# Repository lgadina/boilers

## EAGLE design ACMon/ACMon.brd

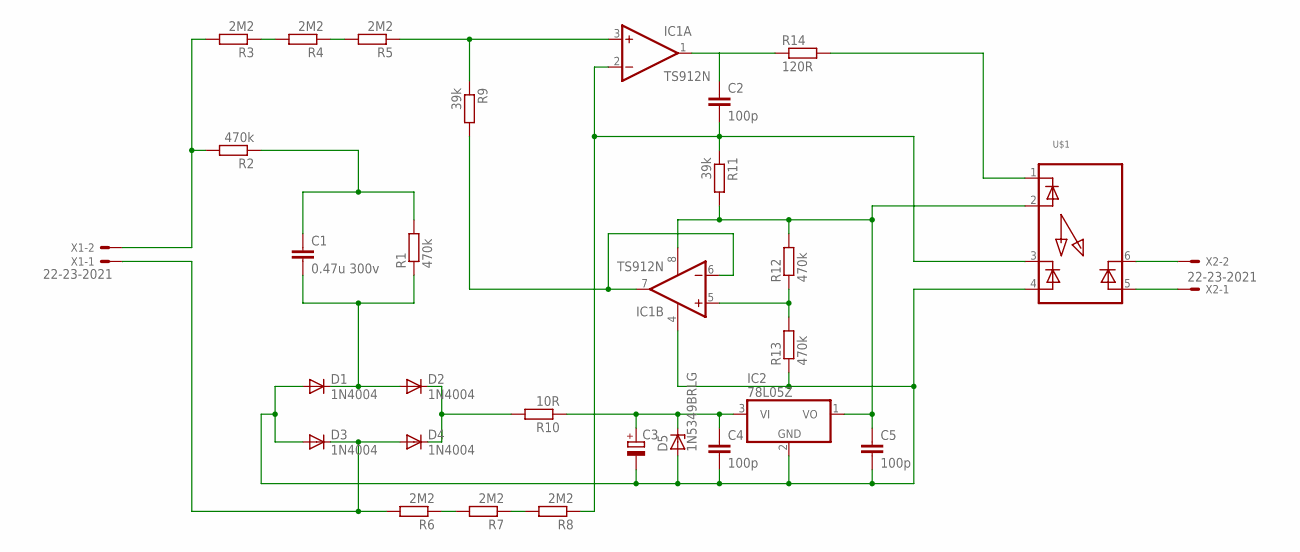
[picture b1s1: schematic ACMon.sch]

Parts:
C1: 0.47u 300v; C275-113X316
C2, C4, C5: 100p; C050-025X075
C3: CPOL-EUE3.5-8; E3,5-8
D1, D2, D3, D4: 1N4004; DO41-10
D5: 1N5349BRLG; DO41Z10
IC1: TS912N; DIL08
IC2: 78L05Z; TO92
R1, R2, R12, R13: 470k; 0309/12
R3, R4, R5, R6, R7, R8: 2M2; 0309/12
R9, R11: 39k; 0309/12
R10: 10R; 0309/12
R14: 120R; 0309/12
U$1: IL300; DIL08
X1, X2: 22-23-2021

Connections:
unnamed: C1.1, R1.2, R2.1
unnamed: C1.2, D1.C, D2.A, R1.1
unnamed: C3.-, C4.2, C5.2, D1.A, D3.A, D5.A, IC1.4 (V-), IC2.2 (GND), R13.1, U$1.4
unnamed: D3.C, D4.A, R6.2, X1.1
unnamed: R6.1, R7.2
unnamed: D2.C, D4.C, R10.2
unnamed: R2.2, R3.2, X1.2
unnamed: R3.1, R4.2
unnamed: R4.1, R5.2
unnamed: IC1.3 (+IN), R5.1, R9.1
unnamed: IC1.6 (-IN), IC1.7 (OUT), R9.2
unnamed: R7.1, R8.2
unnamed: C2.2, IC1.2 (-IN), R8.1, R11.1, U$1.3
unnamed: C2.1, IC1.1 (OUT), R14.1
unnamed: R14.2, U$1.1
unnamed: C3.+, C4.1, D5.C, IC2.3 (VI), R10.1
unnamed: U$1.6, X2.2
unnamed: C5.1, IC1.8 (V+), IC2.1 (VO), R11.2, R12.2, U$1.2
unnamed: U$1.5, X2.1
unnamed: IC1.5 (+IN), R12.1, R13.2

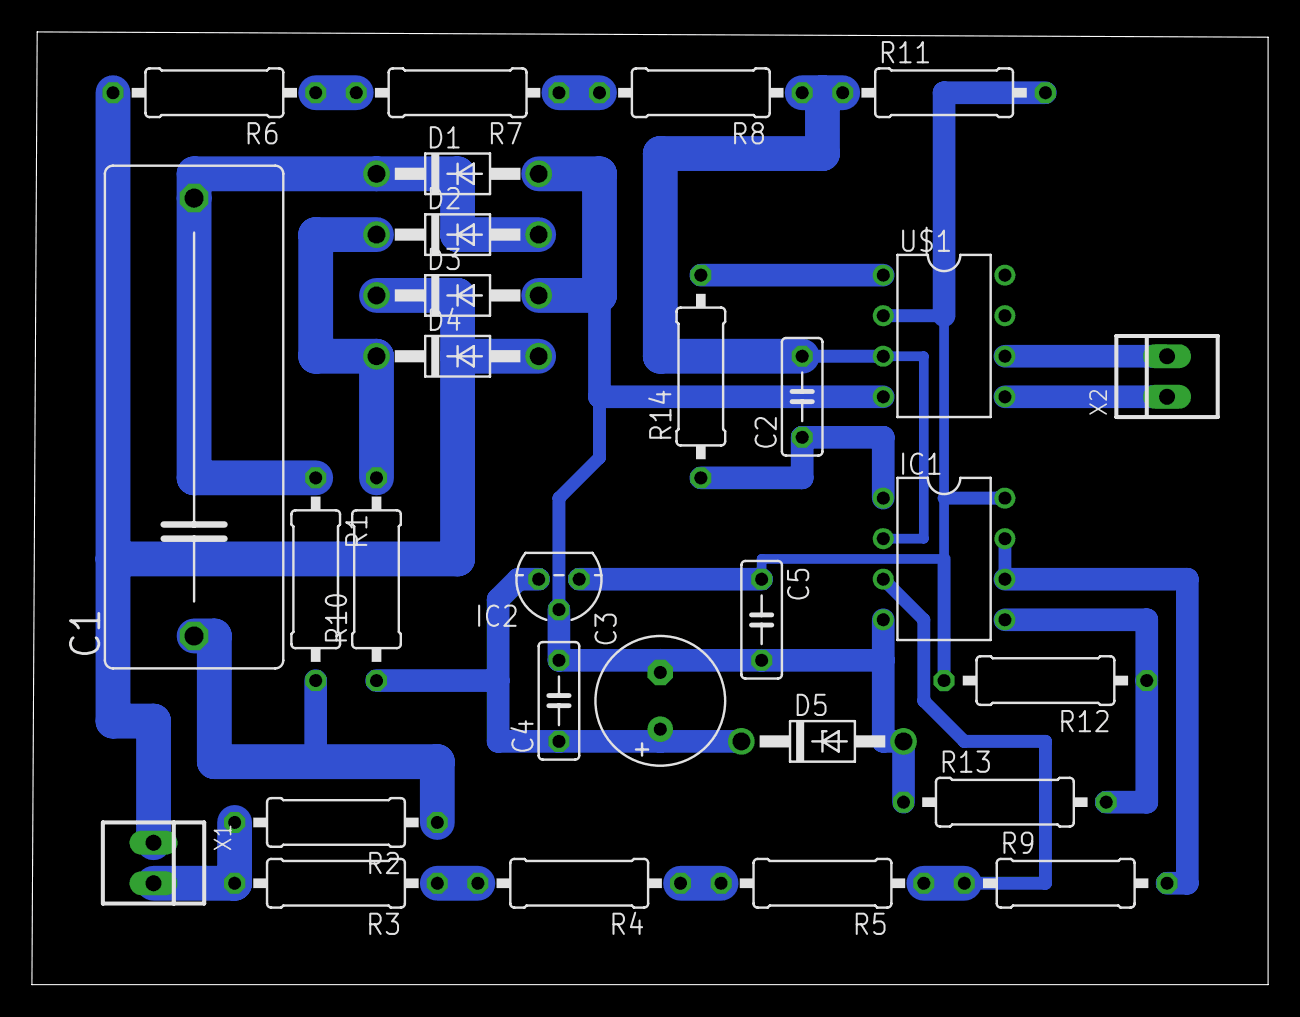
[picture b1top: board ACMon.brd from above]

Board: 2 copper layers, 77.5 x 59.7 mm, 29 parts (0 on the bottom side), 20 nets.

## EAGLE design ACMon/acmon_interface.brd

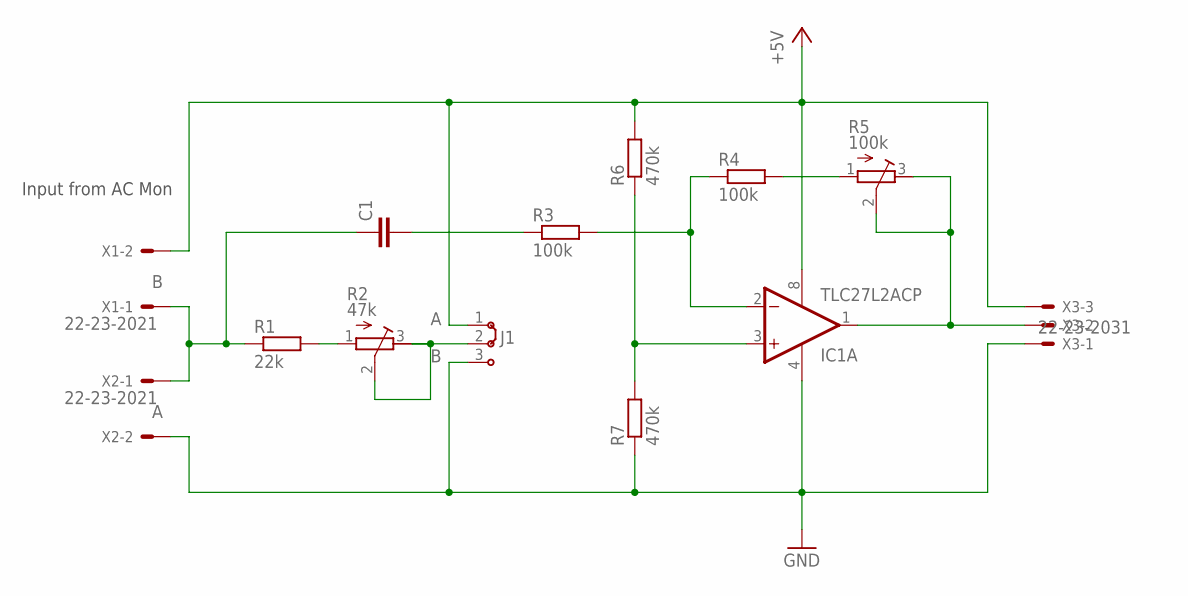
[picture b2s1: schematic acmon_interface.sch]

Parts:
C1: C-EU050-030X075; C050-030X075
IC1: TLC27L2ACP; DIL08
J1: J2X2MM; 04C
R1: 22k; 0207/10
R2: 47k; RTRIM64Y
R3, R4: 100k; 0207/10
R5: 100k; RTRIM64Y
R6, R7: 470k; 0207/10
X1, X2: 22-23-2021
X3: 22-23-2031

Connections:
+5V: IC1.8 (VDD), J1.1, R6.2, X1.2, X3.3
GND: IC1.4 (GND), J1.3, R7.1, X2.2, X3.1
unnamed: J1.2, R2.2 (S), R2.3 (E)
unnamed: R1.2, R2.1 (A)
unnamed: C1.1, R1.1, X1.1, X2.1
unnamed: IC1.2 (-IN), R3.2, R4.1
unnamed: R4.2, R5.1 (A)
unnamed: IC1.1 (OUT), R5.2 (S), R5.3 (E), X3.2
unnamed: C1.2, R3.1
unnamed: IC1.3 (+IN), R6.1, R7.2

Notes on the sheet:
Input from AC Mon

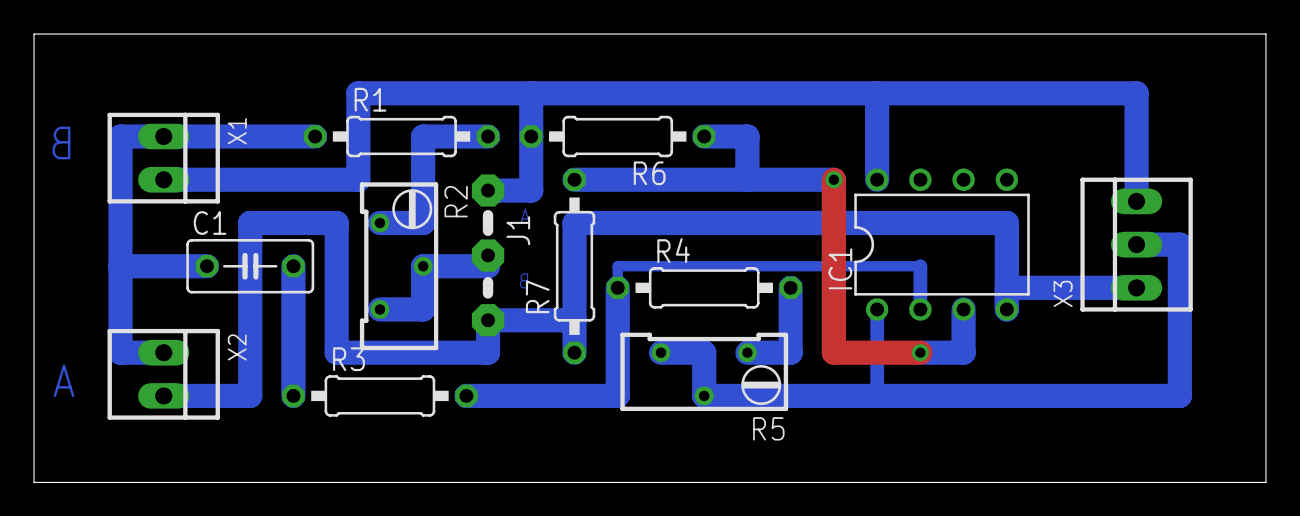
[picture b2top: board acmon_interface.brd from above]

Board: 2 copper layers, 72.4 x 26.3 mm, 13 parts (0 on the bottom side), 10 nets.

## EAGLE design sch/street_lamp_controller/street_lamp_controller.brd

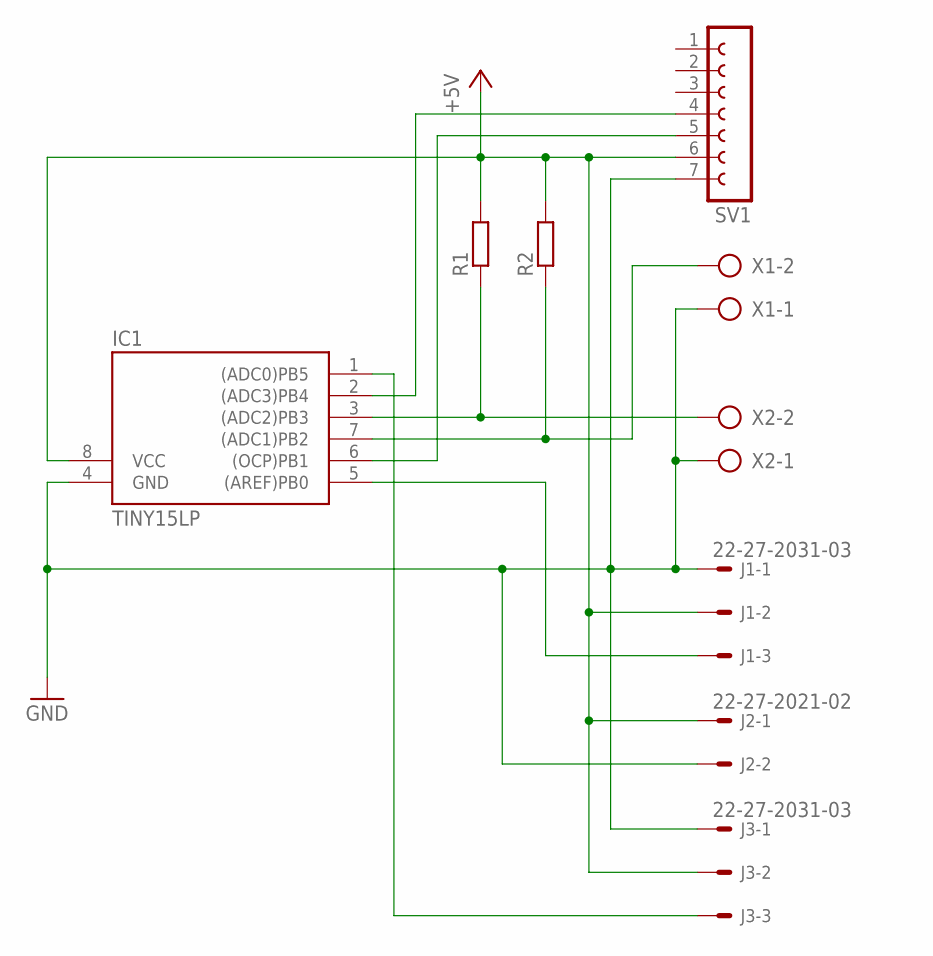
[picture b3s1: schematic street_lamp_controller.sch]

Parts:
IC1: TINY15LP; DIL08
J1, J3: 22-27-2031-03; 6410-03
J2: 22-27-2021-02; 6410-02
R1, R2: R-EU_0204/5; 0204/5
SV1: FE07-1; FE07
X1, X2: AK300/2

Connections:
+5V: IC1.8 (VCC), J1.2, J2.1, J3.2, R1.2, R2.2, SV1.6
GND: IC1.4 (GND), J1.1, J2.2, J3.1, SV1.7, X1.1, X2.1
unnamed: IC1.6 ((OCP)PB1), SV1.5
unnamed: IC1.7 ((ADC1)PB2), R2.1, X1.2
unnamed: IC1.3 ((ADC2)PB3), R1.1, X2.2
unnamed: IC1.5 ((AREF)PB0), J1.3
unnamed: IC1.2 ((ADC3)PB4), SV1.4
unnamed: IC1.1 ((ADC0)PB5), J3.3

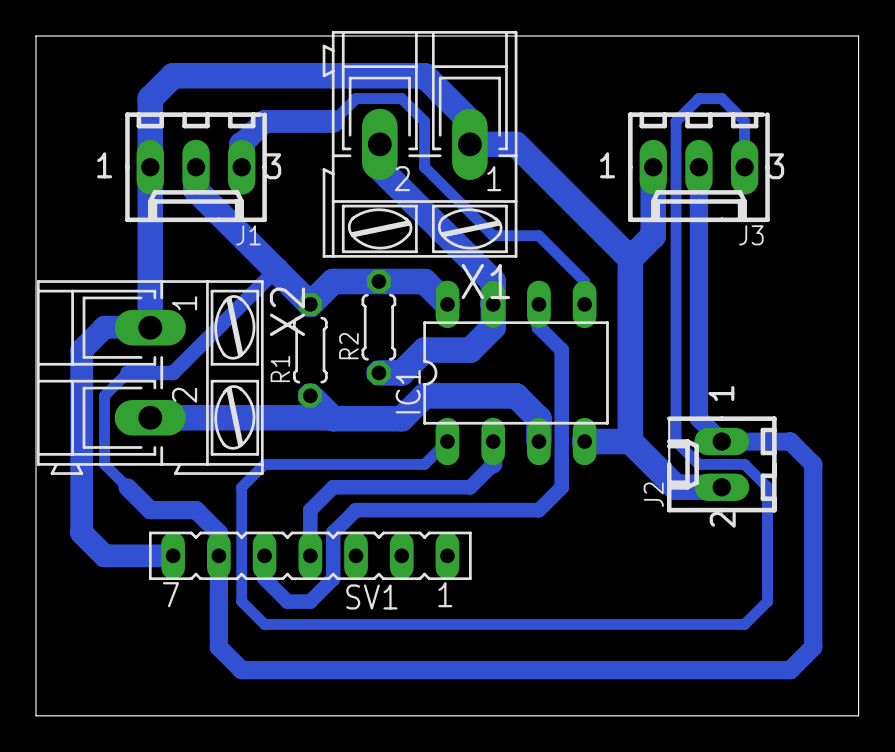
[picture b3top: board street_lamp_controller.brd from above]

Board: 2 copper layers, 45.7 x 37.8 mm, 9 parts (0 on the bottom side), 8 nets.

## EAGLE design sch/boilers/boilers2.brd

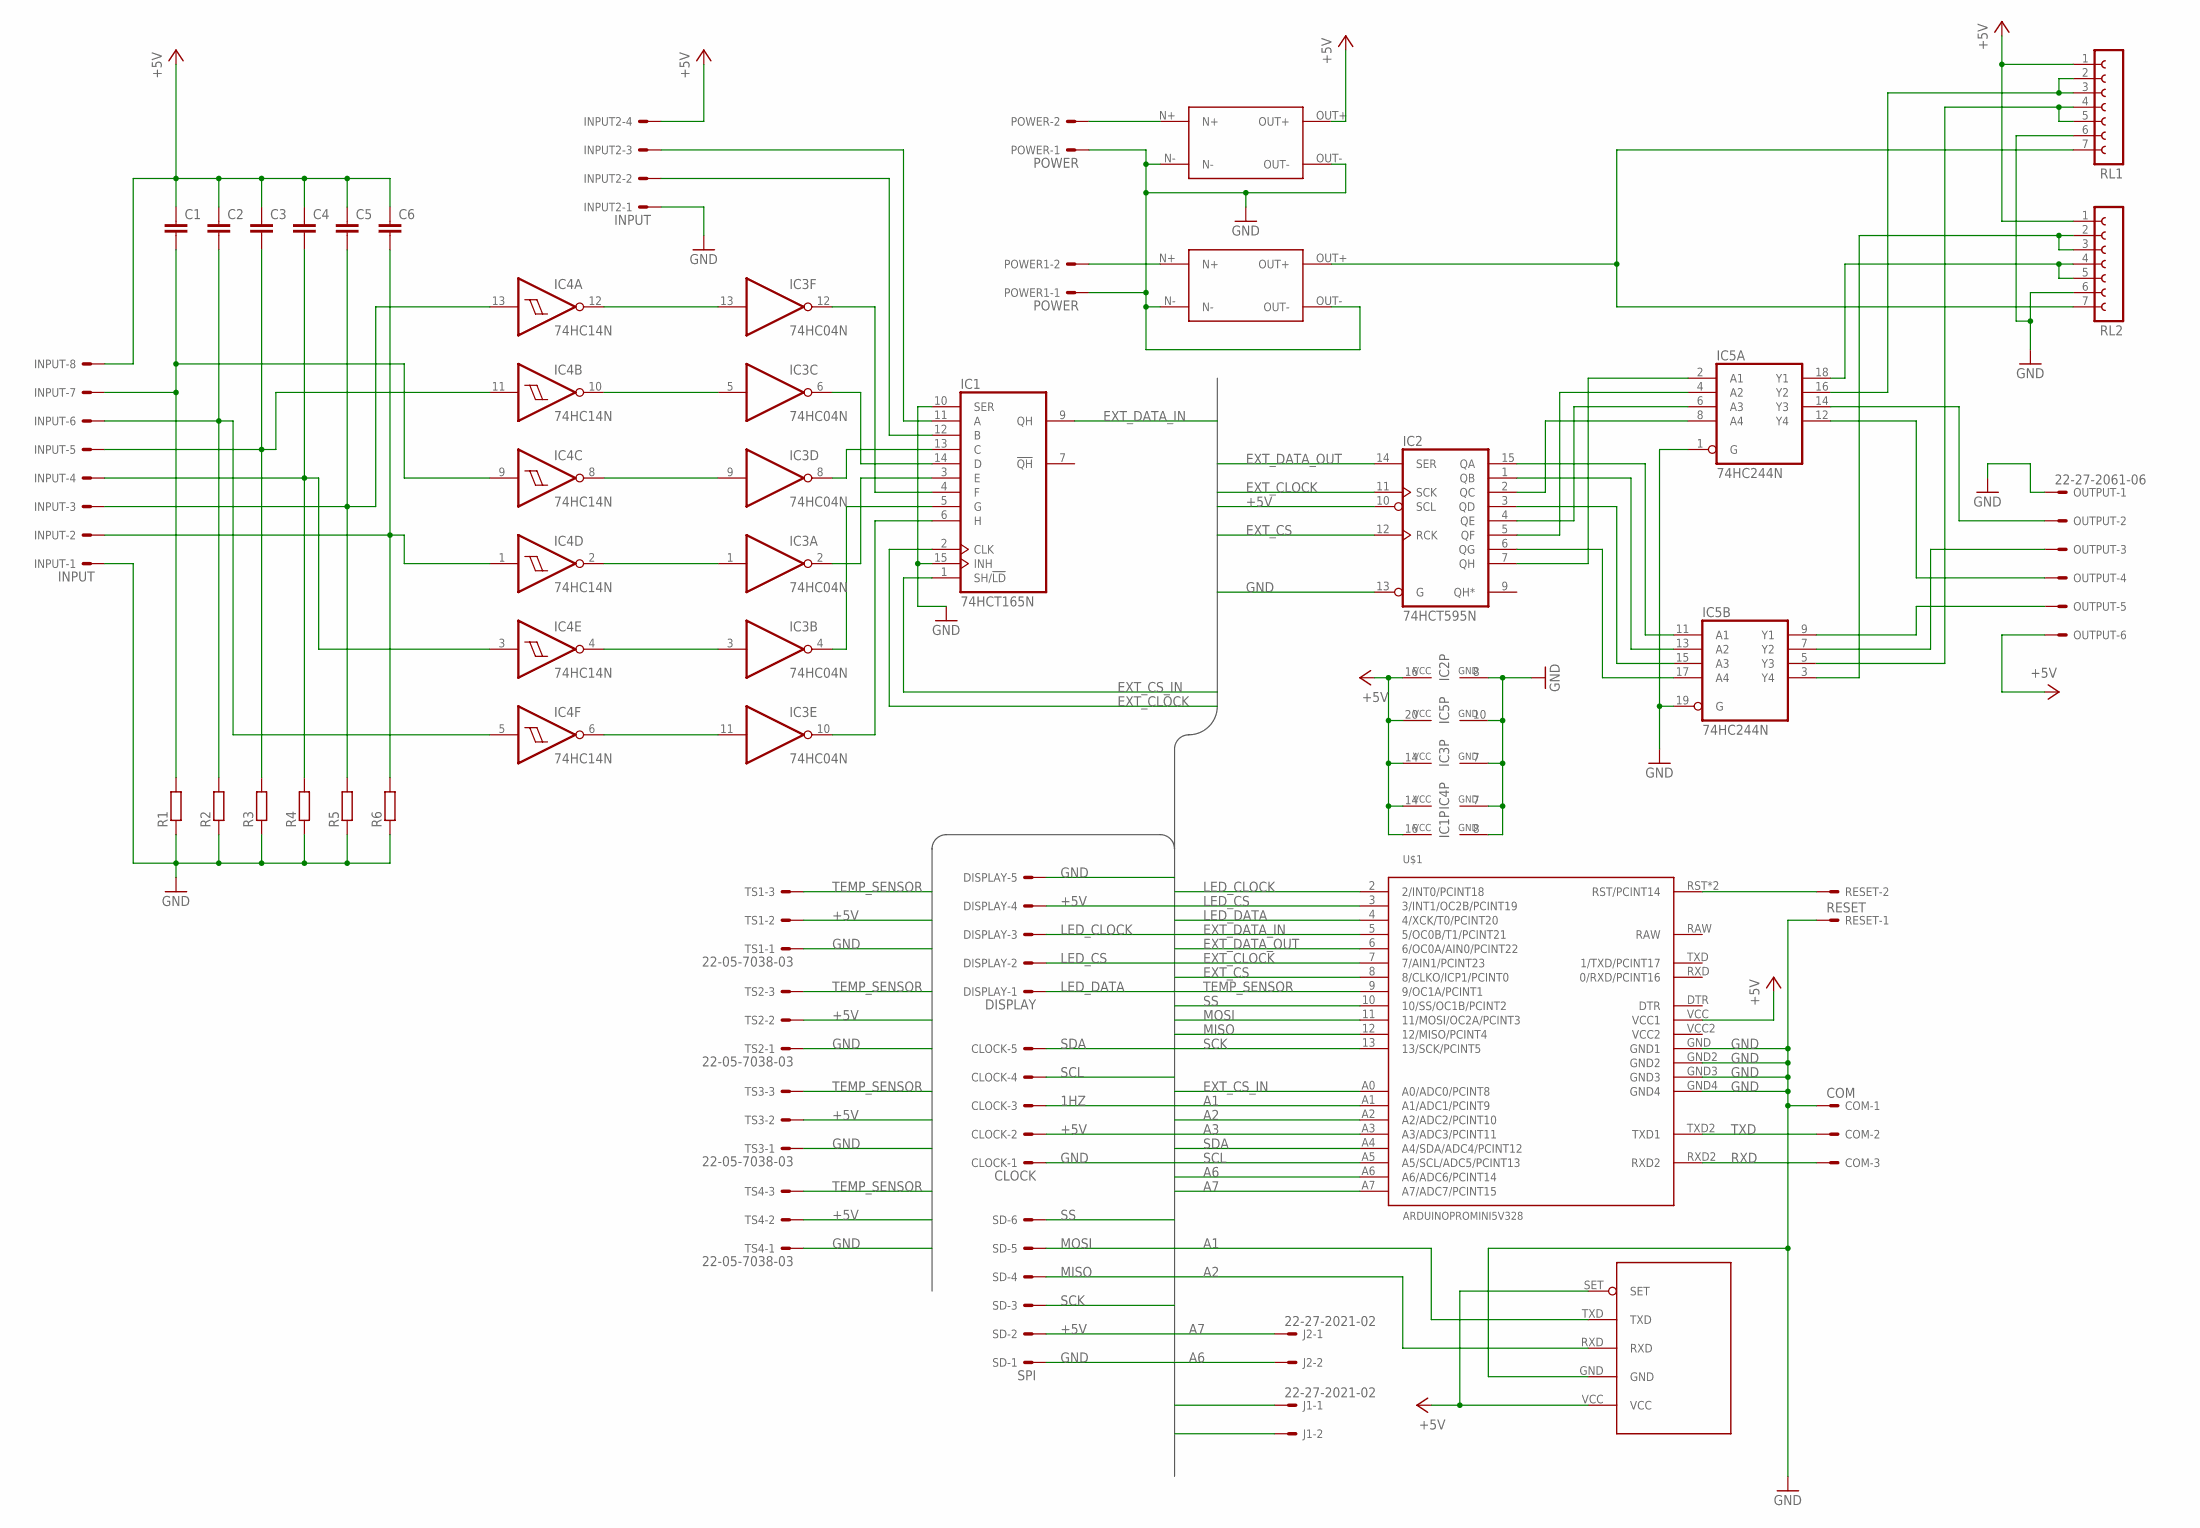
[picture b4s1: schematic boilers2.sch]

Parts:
C1, C2, C3, C4, C5, C6: C-EU050-025X075; C050-025X075
CLOCK: CLOCK; 6410-05
COM: COM; 6410-03
DISPLAY: DISPLAY; 6410-05
IC1: 74HCT165N; DIL16
IC2: 74HCT595N; DIL16
IC3: 74HC04N; DIL14
IC4: 74HC14N; DIL14
IC5: 74HC244N; DIL20
INPUT: INPUT; 6410-08
INPUT2: INPUT; 6410-04
J1, J2: 22-27-2021-02; 6410-02
OUTPUT: 22-27-2061-06; 6410-06
POWER, POWER1: POWER; 6410-02
R1, R2, R3, R4, R5, R6: R-EU_0411/15; 0411/15
RESET: RESET; 6410-02
RL1, RL2: FE07-1; FE07
SD: SPI; 6410-06
TS1, TS2, TS3, TS4: 22-05-7038-03; 7395-03
U$1: ARDUINOPROMINI5V328; ARDUINOMINIPRO5V328
U$4, U$5: 5V_STAB
U$6: HC-11

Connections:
1HZ: CLOCK.3
+5V: C1.1, C2.1, C3.1, C4.1, C5.1, C6.1, CLOCK.2, DISPLAY.4, IC1.16 (VCC), IC2.10 (SCL), IC2.16 (VCC), IC3.14 (VCC), IC4.14 (VCC), IC5.20 (VCC), INPUT.8, INPUT2.4, J1.1, OUTPUT.6, RL1.1, RL2.1, SD.2, TS1.2, TS2.2, TS3.2, TS4.2, U$1.VCC (VCC1), U$4.OUT+, U$6.SET, U$6.VCC
A1: U$1.A1 (A1/ADC1/PCINT9), U$6.TXD
A2: U$1.A2 (A2/ADC2/PCINT10), U$6.RXD
A3: J1.2, U$1.A3 (A3/ADC3/PCINT11)
A6: J2.2, U$1.A6 (A6/ADC6/PCINT14)
A7: J2.1, U$1.A7 (A7/ADC7/PCINT15)
EXT_CLOCK: IC1.2 (CLK), IC2.11 (SCK), U$1.7 (7/AIN1/PCINT23)
EXT_CS: IC2.12 (RCK), U$1.8 (8/CLKO/ICP1/PCINT0)
EXT_CS_IN: IC1.1 (SH/!LD), U$1.A0 (A0/ADC0/PCINT8)
EXT_DATA_IN: IC1.9 (QH), U$1.5 (5/OC0B/T1/PCINT21)
EXT_DATA_OUT: IC2.14 (SER), U$1.6 (6/OC0A/AIN0/PCINT22)
GND: CLOCK.1, COM.1, DISPLAY.5, IC1.8 (GND), IC1.10 (SER), IC1.15 (INH), IC2.8 (GND), IC2.13 (G), IC3.7 (GND), IC4.7 (GND), IC5.1 (G), IC5.10 (GND), IC5.19 (G), INPUT.1, INPUT2.1, OUTPUT.1, POWER.1, POWER1.1, R1.1, R2.1, R3.1, R4.1, R5.1, R6.1, RESET.1, RL1.6, RL2.6, SD.1, TS1.1, TS2.1, TS3.1, TS4.1, U$1.GND (GND1), U$1.GND2, U$1.GND3, U$1.GND4, U$4.N-, U$4.OUT-, U$5.N-, U$5.OUT-, U$6.GND
LED_CLOCK: DISPLAY.3, U$1.2 (2/INT0/PCINT18)
LED_CS: DISPLAY.2, U$1.3 (3/INT1/OC2B/PCINT19)
LED_DATA: DISPLAY.1, U$1.4 (4/XCK/T0/PCINT20)
MISO: SD.4, U$1.12 (12/MISO/PCINT4)
MOSI: SD.5, U$1.11 (11/MOSI/OC2A/PCINT3)
unnamed: IC3.13 (I), IC4.12 (O)
unnamed: IC3.5 (I), IC4.10 (O)
unnamed: IC3.9 (I), IC4.8 (O)
unnamed: IC3.1 (I), IC4.2 (O)
unnamed: IC3.3 (I), IC4.4 (O)
unnamed: IC3.11 (I), IC4.6 (O)
unnamed: IC2.15 (QA), IC5.11 (A1)
unnamed: IC2.1 (QB), IC5.13 (A2)
unnamed: IC2.3 (QD), IC5.15 (A3)
unnamed: IC2.6 (QG), IC5.17 (A4)
unnamed: IC2.7 (QH), IC5.2 (A1)
unnamed: IC2.2 (QC), IC5.8 (A4)
unnamed: IC2.4 (QE), IC5.6 (A3)
unnamed: IC2.5 (QF), IC5.4 (A2)
unnamed: IC1.11 (A), INPUT2.3
unnamed: IC1.5 (G), IC3.4 (O)
unnamed: IC1.6 (H), IC3.10 (O)
unnamed: IC1.3 (E), IC3.2 (O)
unnamed: IC1.13 (C), IC3.8 (O)
unnamed: IC1.14 (D), IC3.6 (O)
unnamed: IC1.4 (F), IC3.12 (O)
unnamed: C1.2, IC4.9 (I), INPUT.7, R1.2
unnamed: C2.2, IC4.5 (I), INPUT.6, R2.2
unnamed: IC1.12 (B), INPUT2.2
unnamed: IC5.16 (Y2), RL1.2, RL1.3
unnamed: C5.2, IC4.13 (I), INPUT.3, R5.2
unnamed: C6.2, IC4.1 (I), INPUT.2, R6.2
unnamed: IC5.3 (Y4), RL2.2, RL2.3
unnamed: C3.2, IC4.11 (I), INPUT.5, R3.2
unnamed: C4.2, IC4.3 (I), INPUT.4, R4.2
unnamed: IC5.18 (Y1), RL2.4, RL2.5
unnamed: IC5.5 (Y3), RL1.4, RL1.5
unnamed: IC5.14 (Y3), OUTPUT.2
unnamed: IC5.7 (Y2), OUTPUT.3
unnamed: IC5.12 (Y4), OUTPUT.4
unnamed: IC5.9 (Y1), OUTPUT.5
unnamed: POWER.2, U$4.N+
unnamed: RL1.7, RL2.7, U$5.OUT+
unnamed: RESET.2, U$1.RST (RST/PCINT14), U$1.RST2 (RST/PCINT14)
unnamed: POWER1.2, U$5.N+
RXD: COM.3, U$1.RXD2
SCK: SD.3, U$1.13 (13/SCK/PCINT5)
SCL: CLOCK.4, U$1.A5 (A5/SCL/ADC5/PCINT13)
SDA: CLOCK.5, U$1.A4 (A4/SDA/ADC4/PCINT12)
SS: SD.6, U$1.10 (10/SS/OC1B/PCINT2)
TEMP_SENSOR: TS1.3, TS2.3, TS3.3, TS4.3, U$1.9 (9/OC1A/PCINT1)
TXD: COM.2, U$1.TXD2 (TXD1)
VCC2: U$1.VCC2

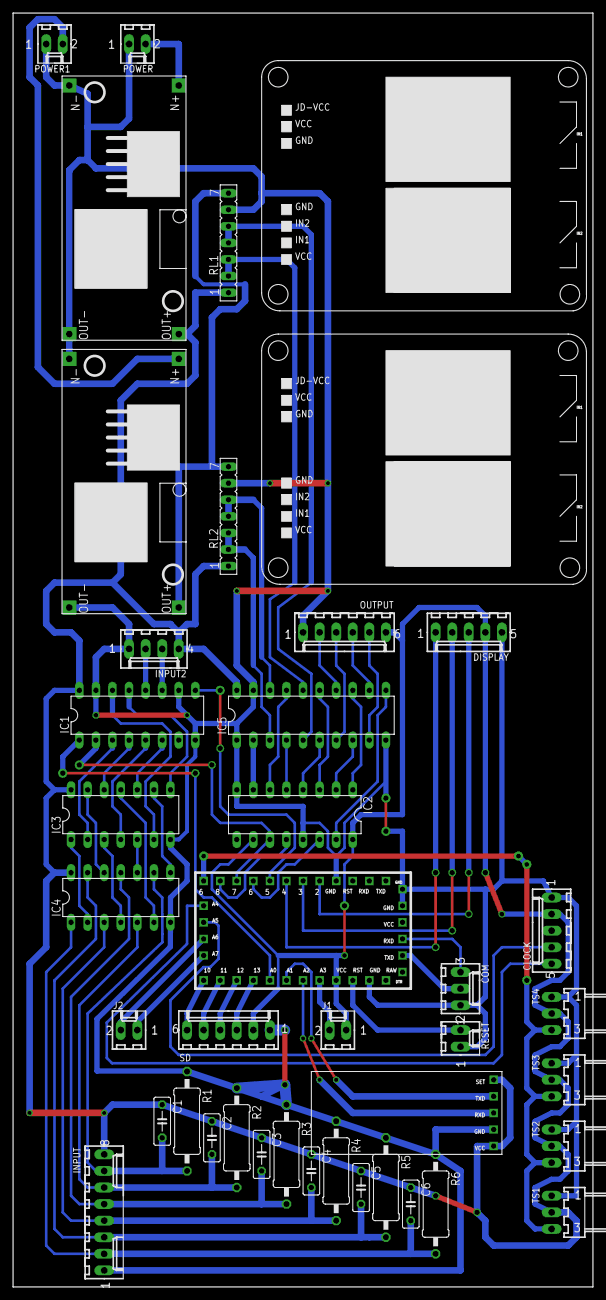
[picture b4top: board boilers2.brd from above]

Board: 2 copper layers, 88.9 x 195.2 mm, 41 parts (0 on the bottom side), 64 nets.

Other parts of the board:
U$2, U$3: 2CHAN_RELAY_5V

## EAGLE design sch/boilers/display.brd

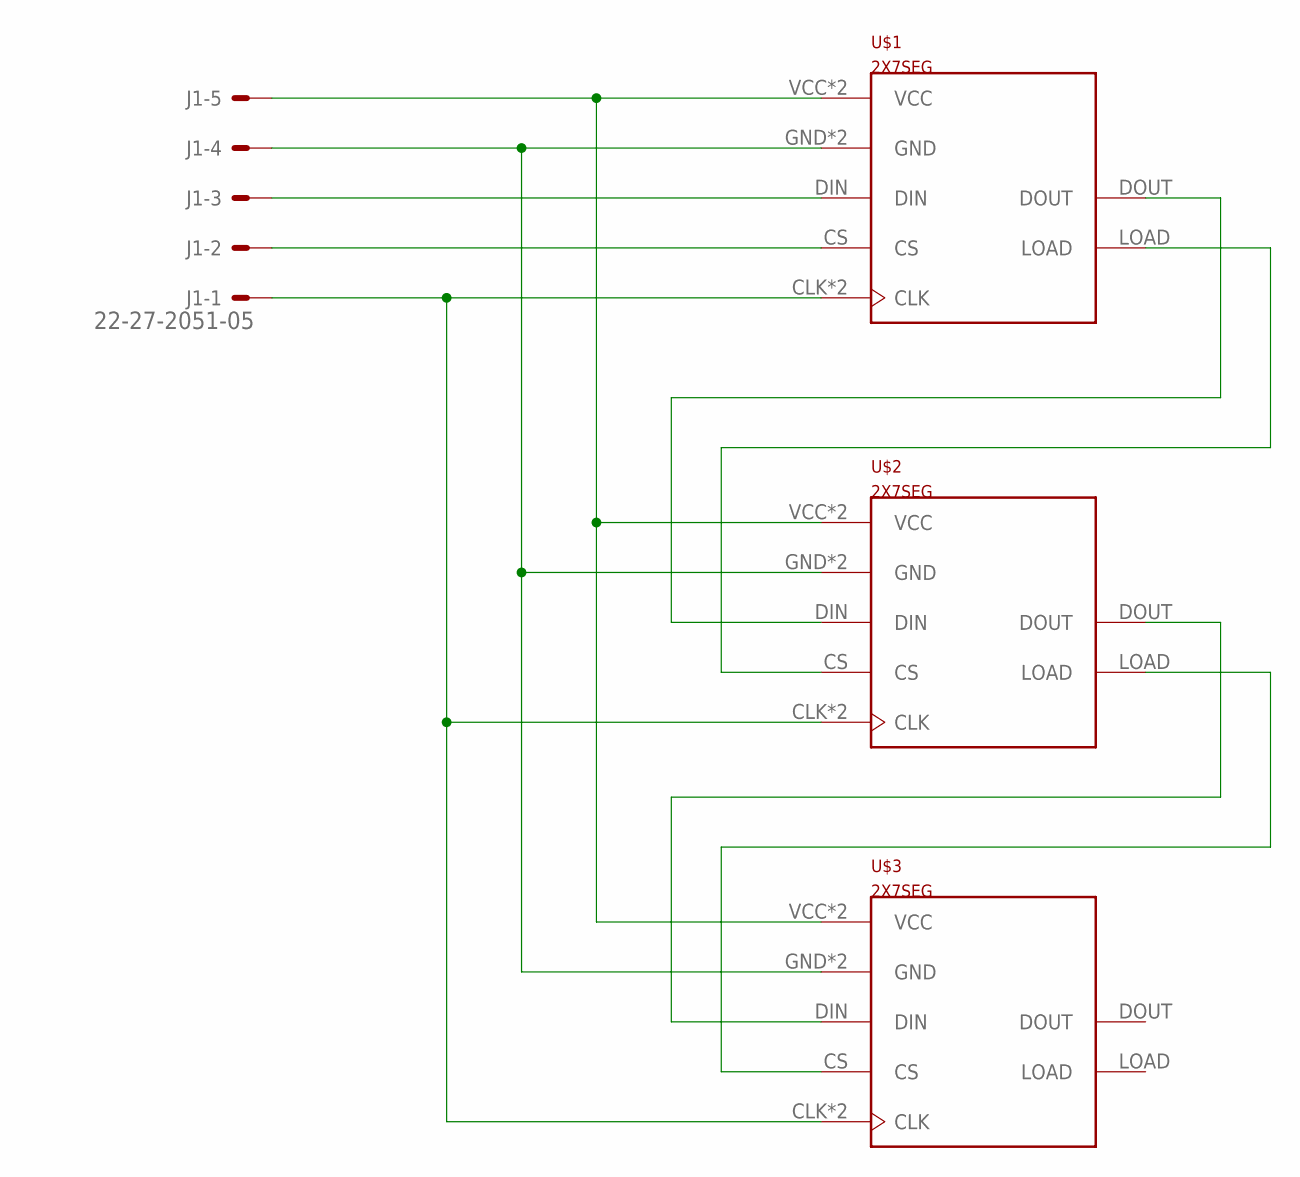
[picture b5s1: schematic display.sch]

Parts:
J1: 22-27-2051-05; 6410-05
U$1, U$2, U$3: 2X7SEG

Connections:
unnamed: J1.5, U$1.VCC, U$1.VCC2 (VCC), U$2.VCC, U$2.VCC2 (VCC), U$3.VCC, U$3.VCC2 (VCC)
unnamed: J1.2, U$1.CS
unnamed: J1.3, U$1.DIN
unnamed: J1.1, U$1.CLK, U$1.CLK2 (CLK), U$2.CLK, U$2.CLK2 (CLK), U$3.CLK, U$3.CLK2 (CLK)
unnamed: U$1.DOUT, U$2.DIN
unnamed: U$1.LOAD, U$2.CS
unnamed: U$2.DOUT, U$3.DIN
unnamed: U$2.LOAD, U$3.CS
unnamed: J1.4, U$1.GND, U$1.GND2 (GND), U$2.GND, U$2.GND2 (GND), U$3.GND, U$3.GND2 (GND)

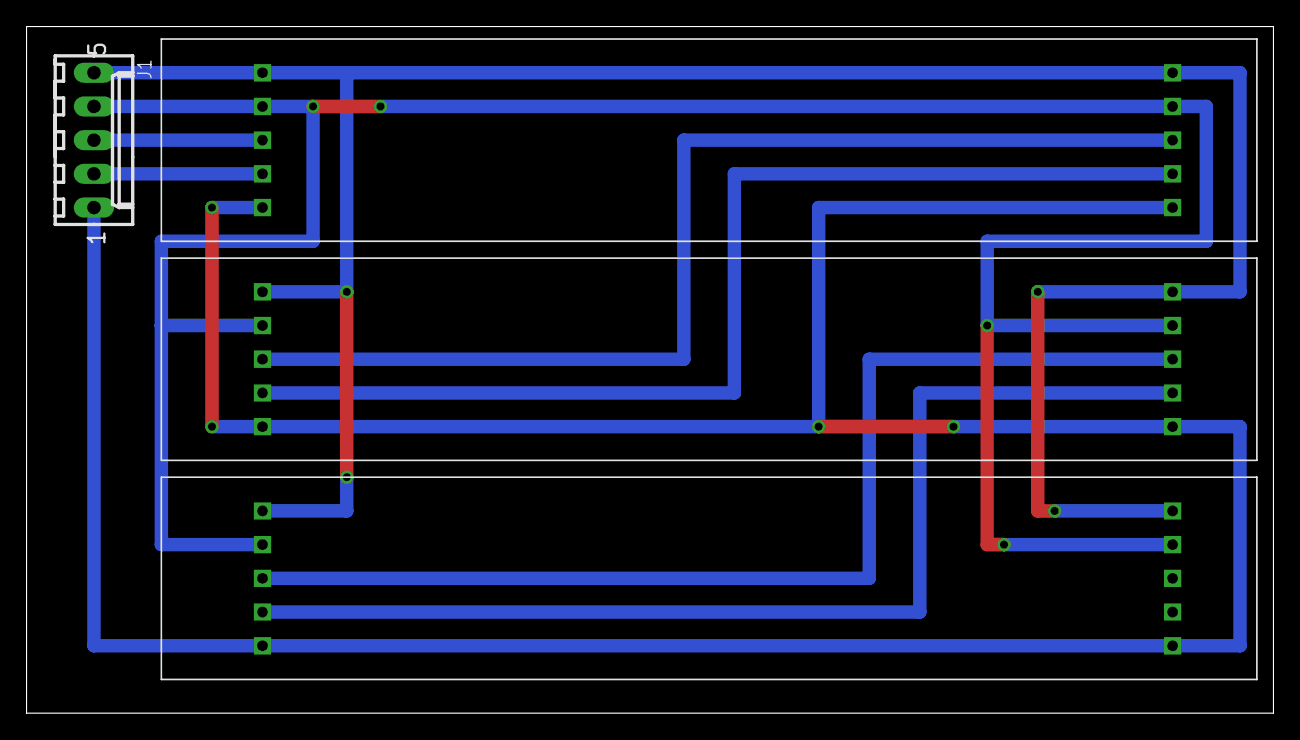
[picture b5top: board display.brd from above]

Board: 2 copper layers, 94.0 x 51.7 mm, 4 parts (0 on the bottom side), 9 nets.

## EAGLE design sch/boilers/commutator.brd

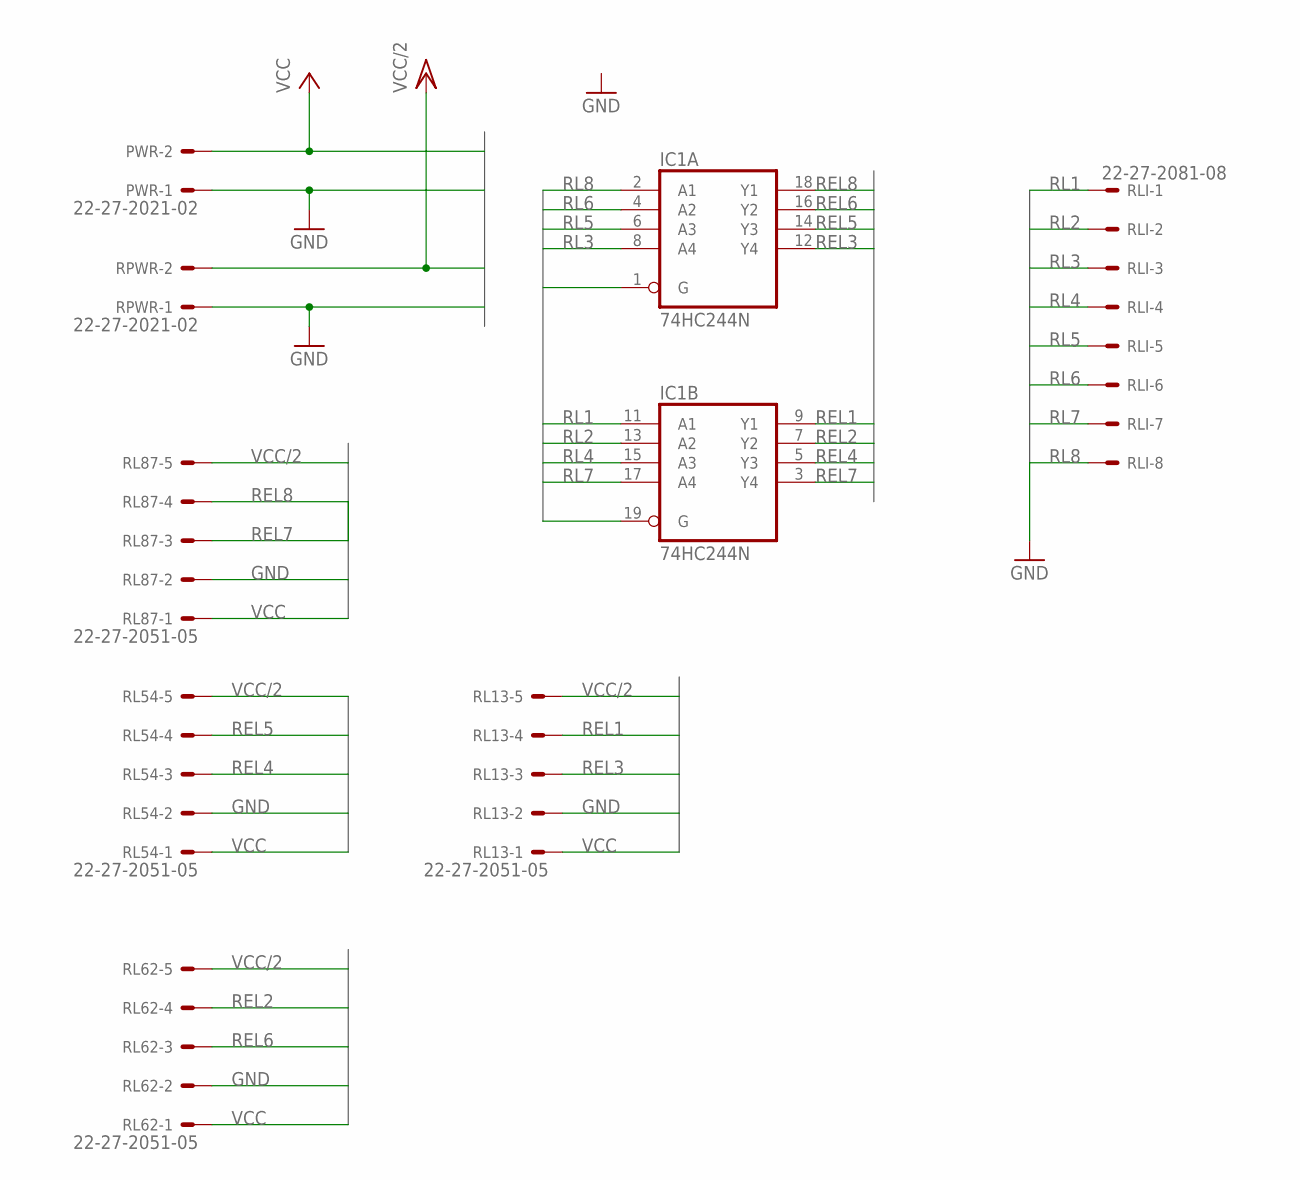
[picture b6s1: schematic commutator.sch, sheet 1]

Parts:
IC1: 74HC244N; DIL20
PWR: 22-27-2021-02; 6410-02
RL13, RL54, RL62, RL87: 22-27-2051-05; 6410-05
RLI: 22-27-2081-08; 6410-08
RPWR: 22-27-2021-02; 6410-02

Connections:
GND: IC1.1 (G), IC1.10 (GND), IC1.19 (G), PWR.1, RL13.2, RL54.2, RL62.2, RL87.2, RPWR.1; also elsewhere on the board
REL1: IC1.9 (Y1), RL13.4
REL2: IC1.7 (Y2), RL62.4
REL3: IC1.12 (Y4), RL13.3
REL4: IC1.5 (Y3), RL54.3
REL5: IC1.14 (Y3), RL54.4
REL6: IC1.16 (Y2), RL62.3
REL7: IC1.3 (Y4), RL87.3
REL8: IC1.18 (Y1), RL87.4
RL1: IC1.11 (A1), RLI.1
RL2: IC1.13 (A2), RLI.2
RL3: IC1.8 (A4), RLI.3
RL4: IC1.15 (A3), RLI.4
RL5: IC1.6 (A3), RLI.5
RL6: IC1.4 (A2), RLI.6
RL7: IC1.17 (A4), RLI.7
RL8: IC1.2 (A1), RLI.8
VCC: IC1.20 (VCC), PWR.2, RL13.1, RL54.1, RL62.1, RL87.1; also elsewhere on the board
VCC/2: RL13.5, RL54.5, RL62.5, RL87.5, RPWR.2

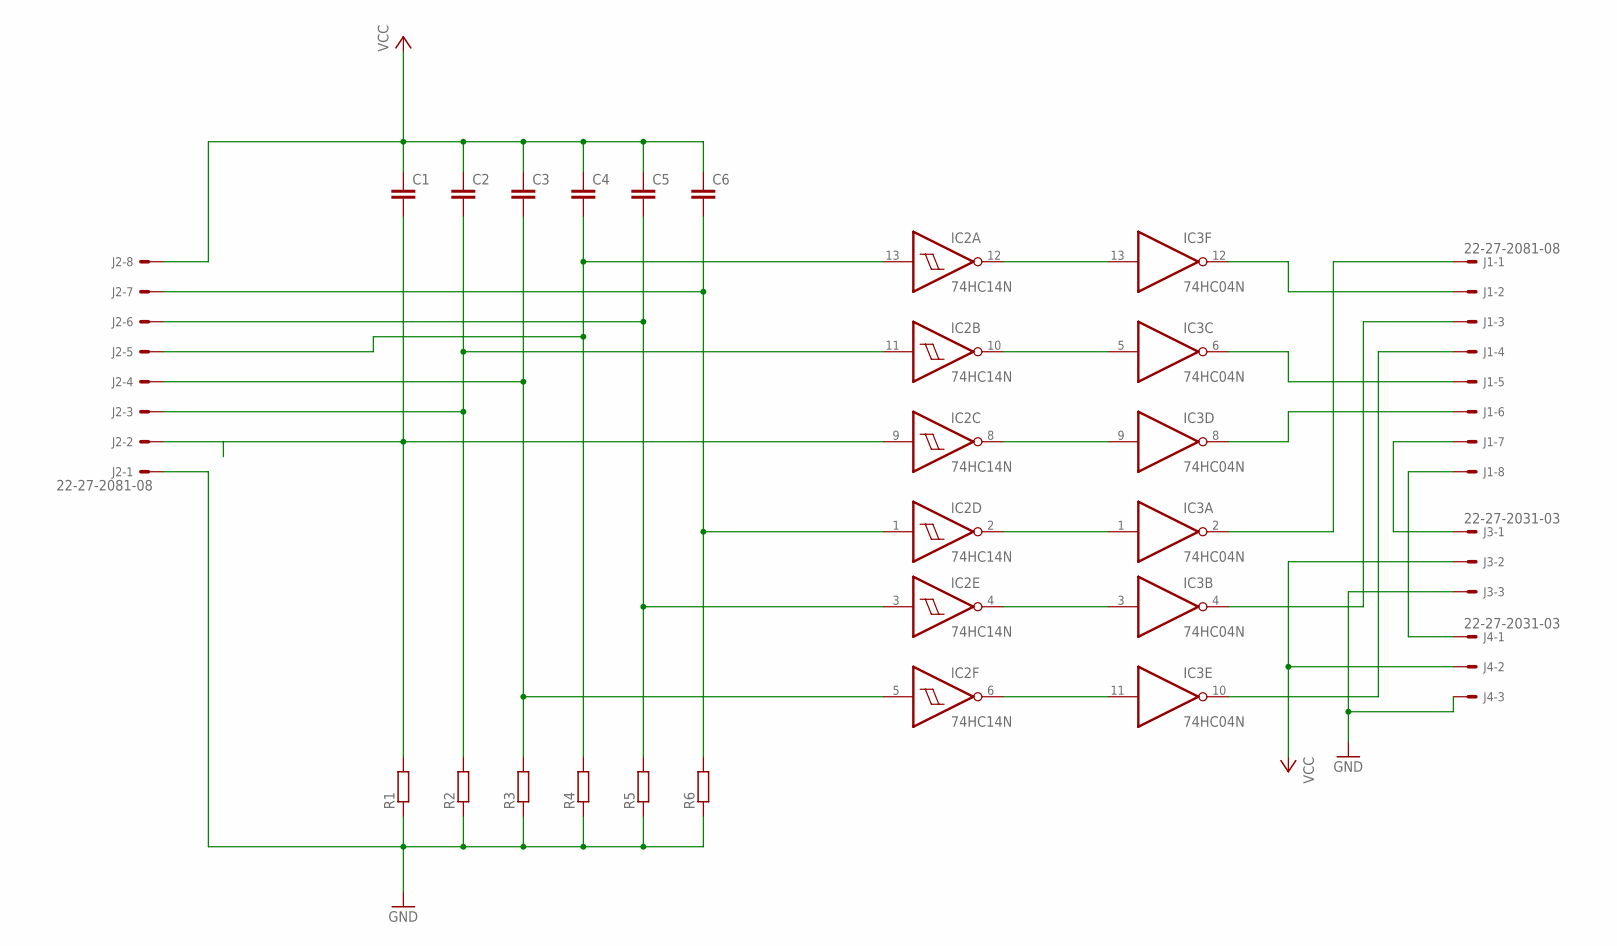
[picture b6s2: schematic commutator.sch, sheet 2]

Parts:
C1, C2, C3, C4, C5, C6: C-EU050-024X044; C050-024X044
IC2: 74HC14N; DIL14
IC3: 74HC04N; DIL14
J1, J2: 22-27-2081-08; 6410-08
J3, J4: 22-27-2031-03; 6410-03
R1, R2, R3, R4, R5, R6: R-EU_0207/15; 0207/15

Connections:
GND: IC2.7 (GND), IC3.7 (GND), J2.1, J3.3, J4.3, R1.1, R2.1, R3.1, R4.1, R5.1, R6.1; also elsewhere on the board
unnamed: IC2.12 (O), IC3.13 (I)
unnamed: IC2.10 (O), IC3.5 (I)
unnamed: IC2.8 (O), IC3.9 (I)
unnamed: IC2.2 (O), IC3.1 (I)
unnamed: IC2.4 (O), IC3.3 (I)
unnamed: IC2.6 (O), IC3.11 (I)
unnamed: IC3.2 (O), J1.1
unnamed: IC3.12 (O), J1.2
unnamed: IC3.4 (O), J1.3
unnamed: IC3.10 (O), J1.4
unnamed: IC3.6 (O), J1.5
unnamed: IC3.8 (O), J1.6
unnamed: C1.2, IC2.9 (I), J2.2, R1.2
unnamed: C2.2, IC2.11 (I), J2.3, R2.2
unnamed: C3.2, IC2.5 (I), J2.4, R3.2
unnamed: C4.2, IC2.13 (I), J2.5, R4.2
unnamed: C5.2, IC2.3 (I), J2.6, R5.2
unnamed: C6.2, IC2.1 (I), J2.7, R6.2
unnamed: J1.7, J3.1
unnamed: J1.8, J4.1
VCC: C1.1, C2.1, C3.1, C4.1, C5.1, C6.1, IC2.14 (VCC), IC3.14 (VCC), J2.8, J3.2, J4.2; also elsewhere on the board

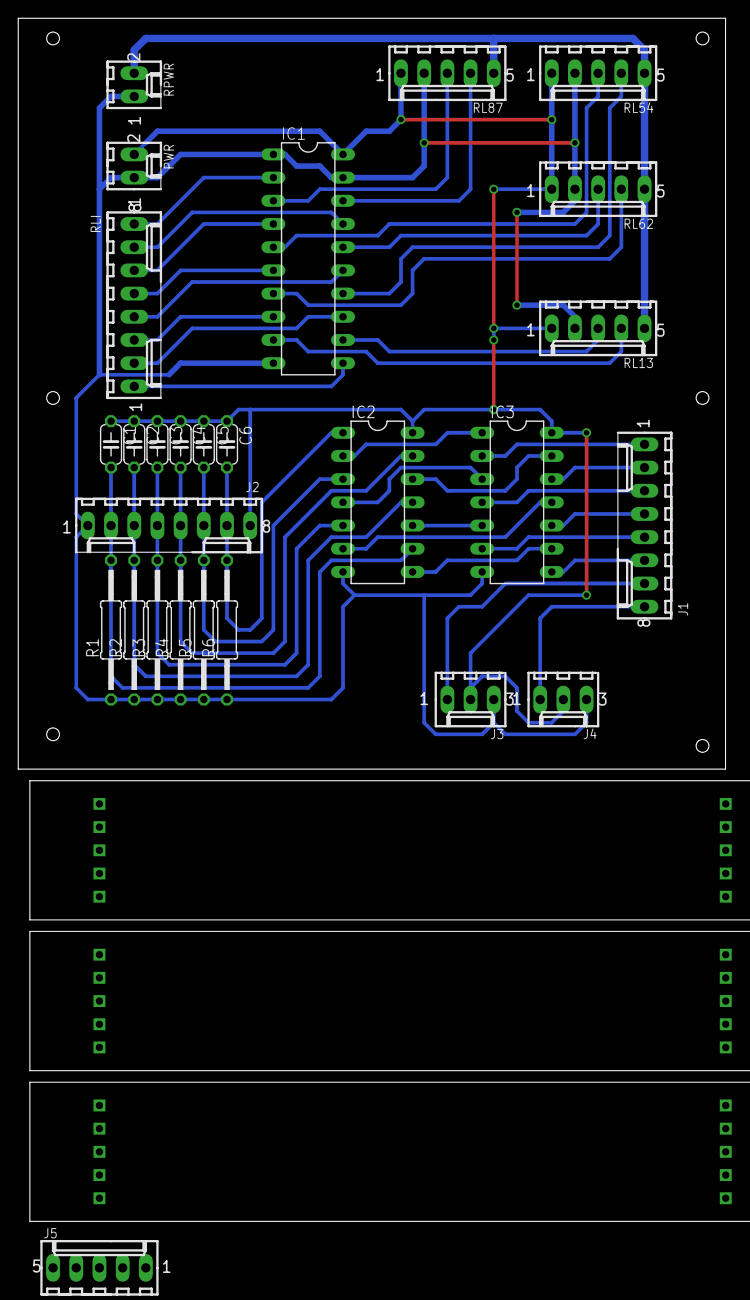
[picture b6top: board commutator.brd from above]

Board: 2 copper layers, 77.5 x 82.2 mm, 30 parts (0 on the bottom side), 48 nets.

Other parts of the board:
J5: 22-27-2051-05; 6410-05
U$1, U$2, U$3: 2X7SEG

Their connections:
unnamed: U$1.DOUT, U$2.DIN
unnamed: U$1.LOAD, U$2.CS
unnamed: J5.1, U$1.CLK, U$1.CLK2, U$2.CLK, U$2.CLK2, U$3.CLK, U$3.CLK2
unnamed: U$2.DOUT, U$3.DIN
unnamed: U$2.LOAD, U$3.CS
unnamed: J5.5, U$1.VCC, U$1.VCC2, U$2.VCC, U$2.VCC2, U$3.VCC, U$3.VCC2
unnamed: J5.4, U$1.GND, U$1.GND2, U$2.GND, U$2.GND2, U$3.GND, U$3.GND2
unnamed: J5.3, U$1.DIN
unnamed: J5.2, U$1.CS
